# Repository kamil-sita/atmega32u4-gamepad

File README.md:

## About project

This repository contains hardware, software and programmable file for my gamepad project based on atmega32u-4.

The gamepad simulates behaviour of a HID keyboard. Joystick always simulates being WASD keys, with pulsating frequency somewhat proportional to the joystick's tilt.
Basic keys simulation can work in 4 working modes:
* mode 0 - JIKL keys
* mode 1 - arrow keys
* mode 2 - Q, E, Left Shift, Left CTRL
* mode 3 - C, G, V, space

You can switch between modes by pressing HWB button. You can reset gamepad by pressing reset button. When holding both of them, the device will enter programmable mode.

If the device is programmed correctly, it will start blinking once resetted/provided with power and after blinking it will register itself as HID keyboard.

### Configuration 

Most of the changes are in Keyboard.c . It should be pretty easy to modify which key strokes are send to the device. You can also modify Descriptors.c to change ManufacturerString and ProductString.

## Device programming

I recommend using dfu-programmer, but FLIP probably also can be used.

## Licence

LUFA [(1)](https://github.com/abcminiuser/lufa), [(2)](http://www.fourwalledcubicle.com/LUFA.php) is under MIT License.

Software for the gamepad is heavily based on LUFA library, and most of the changes are contained inside Keyboard.c and Descriptors.c .
All of my contributions (changes to the library + hardware) are also under MIT License.

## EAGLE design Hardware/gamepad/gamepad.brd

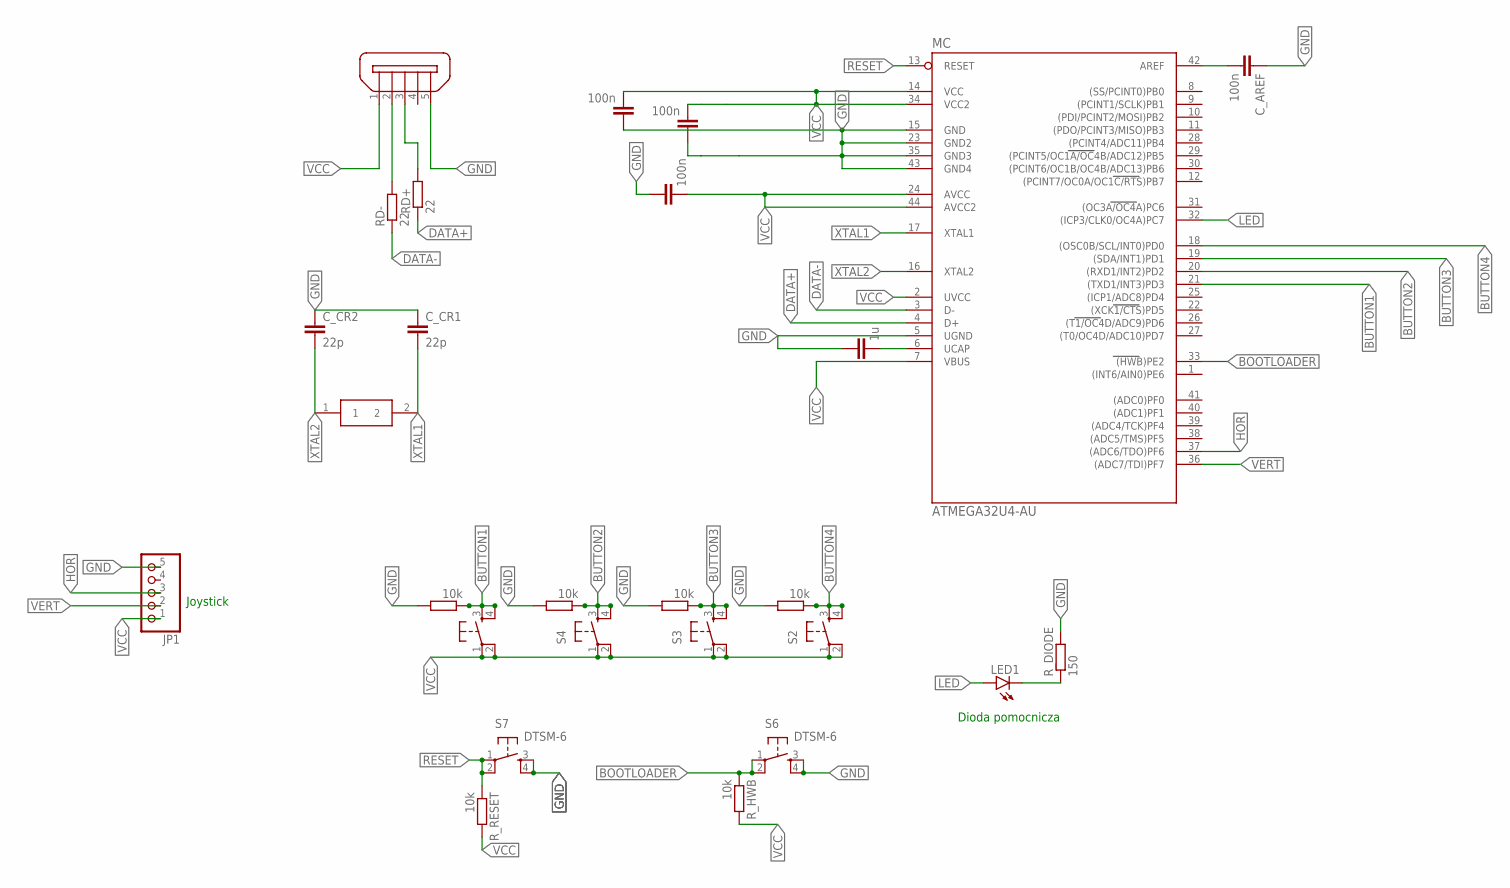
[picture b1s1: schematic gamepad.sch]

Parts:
C_AREF: 100n; C0805
C_CR1, C_CR2: 22p; C0805
C_LPF: 100n; C0805
C_UCAPR: 1u; C0805
C_VCC_TO_GND_14, C_VCC_TO_GND_33: 100n; C0805
JP1: PINHD-1X5; 1X05
LED1: LEDSML1206; SML1206
MC: ATMEGA32U4-AU; TQFP44
QUARTZ_OSC_ZAST: ECS-160-8-30Q-VY-TR; ECS80830QVSTR
RD+: 22; R0805
RD-: 22; R0805
R_DIODE: 150; R2512
R_HWB: 10k; R0805
R_H_SWITCH1, R_H_SWITCH2, R_H_SWITCH3, R_H_SWITCH4: 10k; R0805
R_RESET: 10k; R0805
S2, S3, S4, S5, S6, S7: DTSM-6
X1: ZX62D-B-5PA8

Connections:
BOOTLOADER: MC.33 ((HWB)PE2), R_HWB.1, S6.1, S6.2
BUTTON1: MC.21 ((TXD1/INT3)PD3), R_H_SWITCH1.1, S5.3, S5.4
BUTTON2: MC.20 ((RXD1/INT2)PD2), R_H_SWITCH2.1, S4.3, S4.4
BUTTON3: MC.19 ((SDA/INT1)PD1), R_H_SWITCH3.1, S3.3, S3.4
BUTTON4: MC.18 ((OSC0B/SCL/INT0)PD0), R_H_SWITCH4.1, S2.3, S2.4
DATA+: MC.4 (D+), RD+.1
DATA+CON: RD+.2, X1.3
DATA-: MC.3 (D-), RD-.1
DATA-CON: RD-.2, X1.2
GND: C_AREF.1, C_CR1.1, C_CR2.1, C_LPF.1, C_UCAPR.1, C_VCC_TO_GND_14.1, C_VCC_TO_GND_33.1, JP1.5, MC.5 (UGND), MC.15 (GND), MC.23 (GND2), MC.35 (GND3), MC.43 (GND4), R_DIODE.2, R_H_SWITCH1.2, R_H_SWITCH2.2, R_H_SWITCH3.2, R_H_SWITCH4.2, S6.3, S6.4, S7.3, S7.4, X1.5
HOR: JP1.3, MC.37 ((ADC6/TDO)PF6)
LED: LED1.A, MC.32 ((ICP3/CLK0/OC4A)PC7)
unnamed: LED1.C, R_DIODE.1
unnamed: C_UCAPR.2, MC.6 (UCAP)
unnamed: C_AREF.2, MC.42 (AREF)
RESET: MC.13 (RESET), R_RESET.1, S7.1, S7.2
VCC: C_LPF.2, C_VCC_TO_GND_14.2, C_VCC_TO_GND_33.2, JP1.1, MC.2 (UVCC), MC.7 (VBUS), MC.14 (VCC), MC.24 (AVCC), MC.34 (VCC2), MC.44 (AVCC2), R_HWB.2, R_RESET.2, S2.1, S2.2, S3.1, S3.2, S4.1, S4.2, S5.1, S5.2, X1.1
VERT: JP1.2, MC.36 ((ADC7/TDI)PF7)
XTAL1: C_CR1.2, MC.17 (XTAL1), QUARTZ_OSC_ZAST.2
XTAL2: C_CR2.2, MC.16 (XTAL2), QUARTZ_OSC_ZAST.1

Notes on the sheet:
Joystick
Dioda pomocnicza

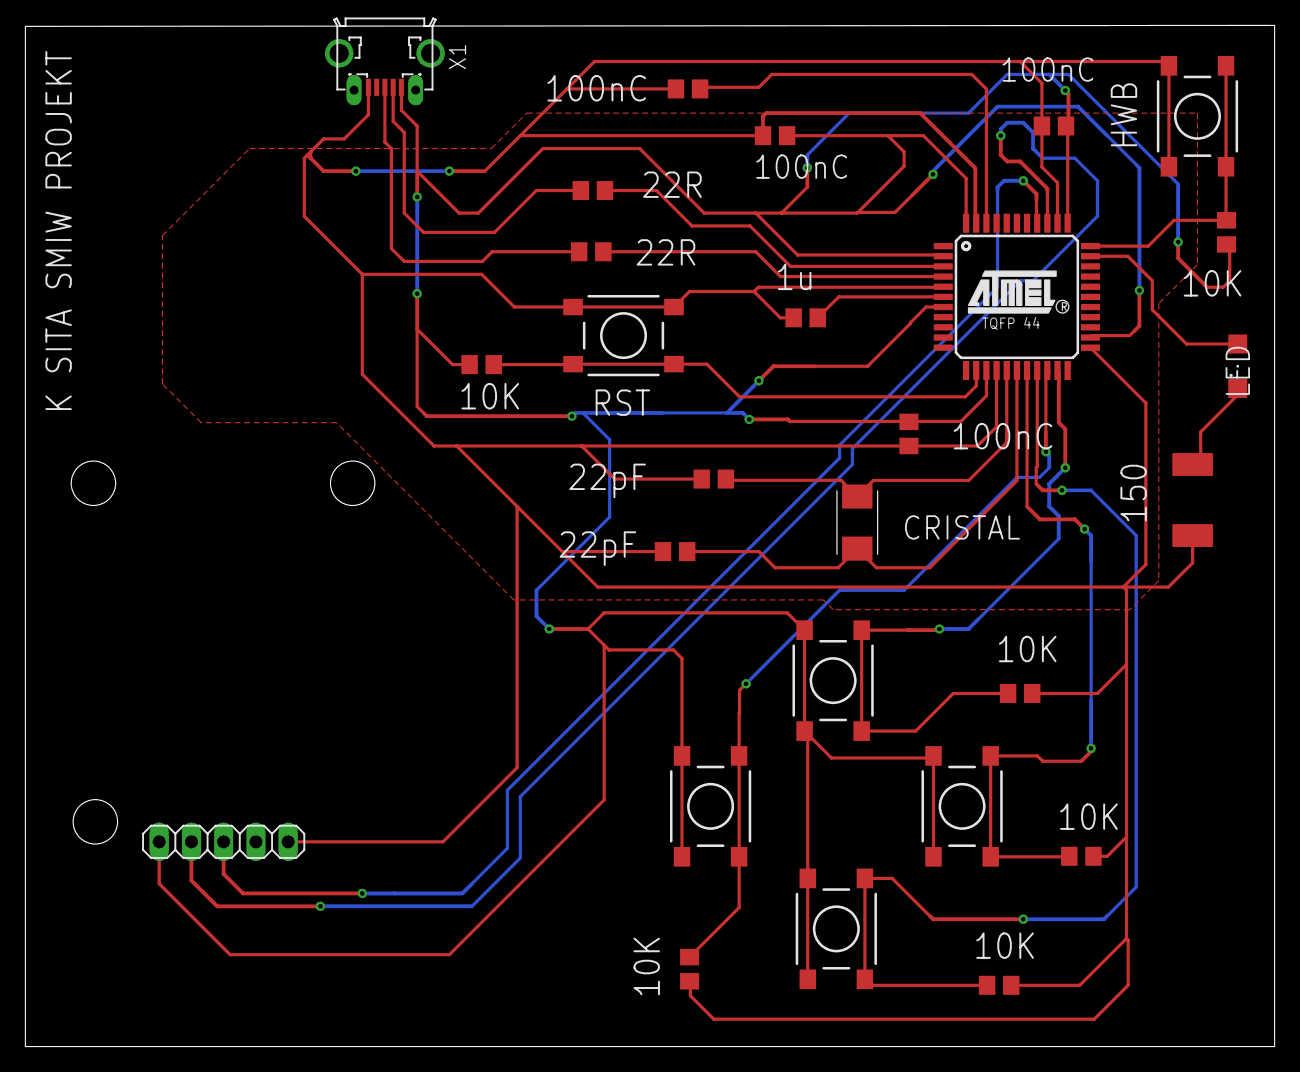
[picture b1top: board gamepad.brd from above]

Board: 2 copper layers, 98.4 x 80.4 mm, 27 parts (0 on the bottom side), 20 nets.

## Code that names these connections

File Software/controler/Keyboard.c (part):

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	DDRC |= (1 << 7);

	//configuration of keys ports
	DDRD &= ~(1<<PD0);
	DDRD &= ~(1<<PD1);
	DDRD &= ~(1<<PD2);
	DDRD &= ~(1<<PD3);

	//adc configuration
	ADCSRA = (1 << ADPS2)|(1 << ADPS1) | (1 << ADPS0); //16MHZ / 128 = 125khz, which is in ADC allowed range of work
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

	//changing working mode
	if (bit_is_clear(PINE, PE2)) {
		button_held_down++;
		if (button_held_down > 16) {
			button_held_down = 16;
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	if (mode == 0) { //mode 0 (JIKL)


		if (bit_is_set(PIND, PD2)) {
			ReportData->KeyCode[UsedKeyCodes++] = HID_KEYBOARD_SC_J;
		}
		if (bit_is_set(PIND, PD3)) {
			ReportData->KeyCode[UsedKeyCodes++] = HID_KEYBOARD_SC_I;
		}
		if (bit_is_set(PIND, PD1)) {
			ReportData->KeyCode[UsedKeyCodes++] = HID_KEYBOARD_SC_K;
		}
		if (bit_is_set(PIND, PD0)) {
			ReportData->KeyCode[UsedKeyCodes++] = HID_KEYBOARD_SC_L;
		}

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			led_blink_disable();
		}

		if (bit_is_set(PIND, PD2)) {
			ReportData->KeyCode[UsedKeyCodes++] = HID_KEYBOARD_SC_LEFT_ARROW;
		}
		if (bit_is_set(PIND, PD3)) {
			ReportData->KeyCode[UsedKeyCodes++] = HID_KEYBOARD_SC_UP_ARROW;
		}
		if (bit_is_set(PIND, PD1)) {
			ReportData->KeyCode[UsedKeyCodes++] = HID_KEYBOARD_SC_DOWN_ARROW;
		}
		if (bit_is_set(PIND, PD0)) {
			ReportData->KeyCode[UsedKeyCodes++] = HID_KEYBOARD_SC_RIGHT_ARROW;
		}

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			led_blink_disable();
		}

		if (bit_is_set(PIND, PD2)) {
			ReportData->KeyCode[UsedKeyCodes++] = HID_KEYBOARD_SC_Q;
		}
		if (bit_is_set(PIND, PD3)) {
			ReportData->Modifier |= HID_KEYBOARD_MODIFIER_LEFTSHIFT;
		}
		if (bit_is_set(PIND, PD1)) {
			ReportData->Modifier |= HID_KEYBOARD_MODIFIER_LEFTCTRL;
		}
		if (bit_is_set(PIND, PD0)) {
			ReportData->KeyCode[UsedKeyCodes++] = HID_KEYBOARD_SC_E;
		}
	}else if (mode == 3) { // mode 3 (C, G, V, Space)
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			led_blink_disable();
		}

		if (bit_is_set(PIND, PD2)) {
			ReportData->KeyCode[UsedKeyCodes++] = HID_KEYBOARD_SC_C;
		}
		if (bit_is_set(PIND, PD3)) {
			ReportData->KeyCode[UsedKeyCodes++] = HID_KEYBOARD_SC_G;
		}
		if (bit_is_set(PIND, PD1)) {
			ReportData->KeyCode[UsedKeyCodes++] = HID_KEYBOARD_SC_SPACE;
		}
		if (bit_is_set(PIND, PD0)) {
			ReportData->KeyCode[UsedKeyCodes++] = HID_KEYBOARD_SC_V;
		}
	}
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
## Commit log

2021-02-19 initial load

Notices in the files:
Software/controler/Keyboard.c:
Copyright (C) Dean Camera, 2017.
Copyright 2017  Dean Camera (dean [at] fourwalledcubicle [dot] com)
Copyright 2010  Denver Gingerich (denver [at] ossguy [dot] com)
